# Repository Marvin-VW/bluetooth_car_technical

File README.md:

# 3D-Printed ESP32 RC Car – Complete Project Documentation

## Project Overview
This project consists of a fully 3D-printed RC car based on an ESP32 controller, designed for remote control via a custom-built app.  
All mechanical parts, electronics (PCBs), and software components are fully self-developed or heavily customized.

The vehicle body is based on a DeLorean model (Back to the Future), which has been modified for integration of custom hardware components and a clear interior view.

---

## Features
- **Drive System**:
    - JGB37-520 Motor connected via an axle with ball bearings
    - Front axle controlled by MG90S servo
- **Distance Sensors**:
    - 3x VL53L0X laser distance sensors connected via I2C bus
- **Camera**:
    - ESP32-CAM module for live video streaming over WiFi
- **Lighting**:
    - WS2812C individually addressable LEDs for headlights, taillights, indicators, brake lights, and reverse lights
- **Battery**:
    - 2x Samsung SDI INR18650-35E 3.7V cells (combined to 7.2V system)
- **Charging**:
    - USB-C PD (Power Delivery) charging at 9V/3A via custom charging module
- **Battery Management System (BMS)**:
    - HX-2S-D20 unit for safe charging/discharging

---

## Mechanical Design
- **Chassis**: Modified base from DKS Basics, adjusted for optimized motor mounts, axle supports, battery placement, ESP32 mounting, and PCB integration.
- **Body**: DeLorean STL, modified for wheel clearance, USB-C charging access, and removal of windows for better visibility of internal components.
- **3D Printed Parts**:
    - Chassis components
    - Gear holders and servo brackets
    - Motor mounts
    - Sensor mounts
    - Battery compartments
    - LED lighting holders

---

## Bill of Materials (BOM)

| Component                   | Description                                           |
|------------------------------|-------------------------------------------------------|
| ESP32                        | Main microcontroller                                 |
| JGB37-520 Motor              | Drive motor                                           |
| MG90S Servo                  | Steering servo                                        |
| 3x VL53L0X                   | Distance sensors (I2C bus)                           |
| 2x Samsung INR18650-35E      | Battery cells                                         |
| INA3221                      | Triple current monitor                               |
| HX-2S-D20                    | 2S BMS for battery management                        |
| ESP32-CAM                    | Camera module                                         |
| WS2812C LED Strip            | Addressable LEDs for lighting                        |
| Custom Power PCB             | Power regulation and distribution board             |
| Custom ESP32 PCB             | ESP32 interface board                               |
| Front LED PCBs (x2 variants) | Strip & individual LED board for front lighting      |
| Rear LED PCBs (x2 variants)  | Strip & individual LED board for rear lighting       |
| 3D Printed Parts             | Chassis, body, mounting structures                   |
| USB-C Charging Module        | USB-PD fast charging support                         |
| Bearings, Gears, Shafts      | Mechanical components                               |

---

## Repository Structure

```bash
/3d-printed-esp32-rc-car
│
├── 3d_printed_parts/             # STL files for chassis and case
│
├── pcbs/
│   ├── power_pcb/                # KiCad files and Gerbers for power management board
│   ├── esp32_pcb/                # KiCad files and Gerbers for ESP32 connection board
│   ├── lighting_pcbs/
│   │   ├── front_strip_version/  # PCB for front LED strip mounting
│   │   ├── front_single_led/     # PCB for front individual LEDs
│   │   ├── rear_strip_version/   # PCB for rear LED strip mounting
│   │   └── rear_single_led/      # PCB for rear individual LEDs
│
├── firmware/                     # (External Link: [ESP32 Firmware Repo](https://github.com/Marvin-VW/bluetooth_car_cpp))
│
├── app/                          # (External Link: [Mobile App Repo](https://github.com/Marvin-VW/spring_rest_todo_app))
│
├── images/                       # Photos, renderings, diagrams
│
└── README.md                     # This file
```

---

## Electronic Architecture

### Main Boards:
- **Power PCB**:
    - Battery management (charging/discharging)
    - 5V and 6.6V regulated outputs
    - INA3221 triple current sensor
    - Connectors for servo, distance sensors, motor
- **ESP32 PCB**:
    - Dedicated ESP32 interface
    - Connection to power PCB via a 2x7 (14-pin) connector

### Lighting Boards:
- **Front LED Boards**:
    - *LED Strip Version*: For easier integration of flexible LED strips (WS2812C-compatible)
    - *Individual LED Version*: For precise placement of discrete WS2812C LEDs
- **Rear LED Boards**:
    - *LED Strip Version*
    - *Individual LED Version*

Each lighting board is tailored to fit into designated 3D printed holders.

---

Note: Pins not accurate.

---

## Build and Assembly

1. **3D Print Parts**  
   Print all required STL files using PLA or PETG for maximum durability.

2. **Assemble Electronics**
    - Solder PCBs based on provided KiCad projects.
    - Install the Power PCB, ESP32 PCB, distance sensors, and LEDs.

3. **Mechanical Assembly**
    - Mount motor, servo, and axles with ball bearings.
    - Install batteries, boards, and secure the chassis components.

4. **Install Firmware**
    - Flash the ESP32 using the firmware available in the firmware repository.

5. **App Setup**
    - Install the mobile app to control the car via WiFi.

6. **Testing and Calibration**
    - Test motor, servo, sensors, and LEDs individually before full operation.

---

## License
MIT License

---

## Contributions
Contributions, issues, and feature requests are welcome! Feel free to check the [issues page](#).

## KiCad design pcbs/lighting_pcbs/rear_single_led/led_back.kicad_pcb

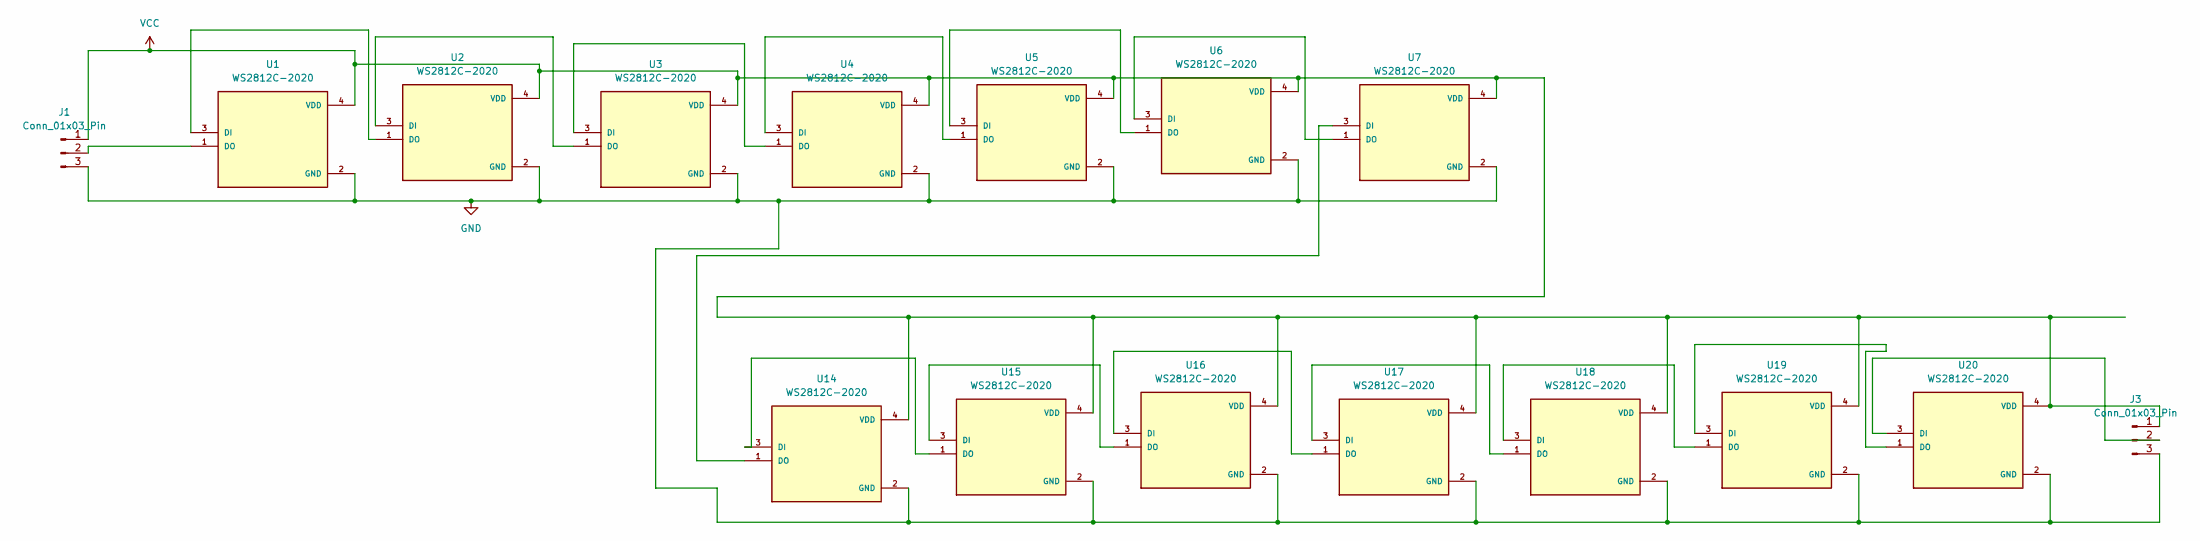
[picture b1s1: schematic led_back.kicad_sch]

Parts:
J1, J3: Conn_01x03_Pin; PinHeader_1x03_P2.54mm_Vertical
U1, U2, U3, U4, U5, U6, U7, U14, U15, U16, U17, U18, U19, U20: WS2812C-2020; LED_WS2812C-2020; PARTREV V1.0

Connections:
GND: J1.3, J3.3, U1.2 (GND), U2.2 (GND), U3.2 (GND), U4.2 (GND), U5.2 (GND), U6.2 (GND), U7.2 (GND), U14.2 (GND), U15.2 (GND), U16.2 (GND), U17.2 (GND), U18.2 (GND), U19.2 (GND), U20.2 (GND)
unnamed: J1.2, U1.1 (DO)
unnamed: J3.2, U20.3 (DI)
unnamed: U1.3 (DI), U2.1 (DO)
unnamed: U2.3 (DI), U3.1 (DO)
unnamed: U3.3 (DI), U4.1 (DO)
unnamed: U4.3 (DI), U5.1 (DO)
unnamed: U5.3 (DI), U6.1 (DO)
unnamed: U6.3 (DI), U7.1 (DO)
unnamed: U14.3 (DI), U15.1 (DO)
unnamed: U7.3 (DI), U14.1 (DO)
unnamed: U15.3 (DI), U16.1 (DO)
unnamed: U16.3 (DI), U17.1 (DO)
unnamed: U17.3 (DI), U18.1 (DO)
unnamed: U18.3 (DI), U19.1 (DO)
unnamed: U19.3 (DI), U20.1 (DO)
VCC: J1.1, J3.1, U1.4 (VDD), U2.4 (VDD), U3.4 (VDD), U4.4 (VDD), U5.4 (VDD), U6.4 (VDD), U7.4 (VDD), U14.4 (VDD), U15.4 (VDD), U16.4 (VDD), U17.4 (VDD), U18.4 (VDD), U19.4 (VDD), U20.4 (VDD)

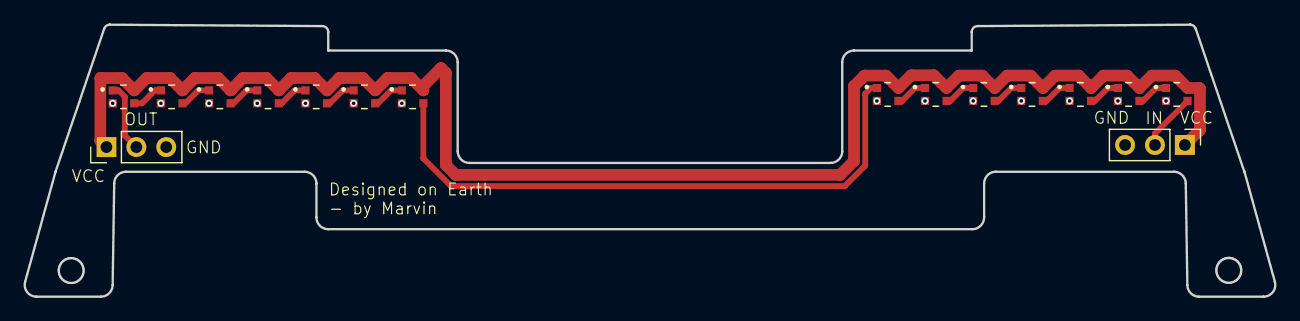
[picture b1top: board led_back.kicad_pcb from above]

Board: 2 copper layers, 106.2 x 23.1 mm, 16 parts (0 on the bottom side), 17 nets.

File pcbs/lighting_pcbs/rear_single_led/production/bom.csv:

Designator,Footprint,Quantity,Value,LCSC Part #
"_2, ",,2,,
"J1, J3",PinHeader_1x03_P2.54mm_Vertical,2,Conn_01x03_Pin,
"U1, U14, U15, U16, U17, U18, U19, U2, U20, U3, U4, U5, U6, U7",LED_WS2812C-2020,14,WS2812C-2020,

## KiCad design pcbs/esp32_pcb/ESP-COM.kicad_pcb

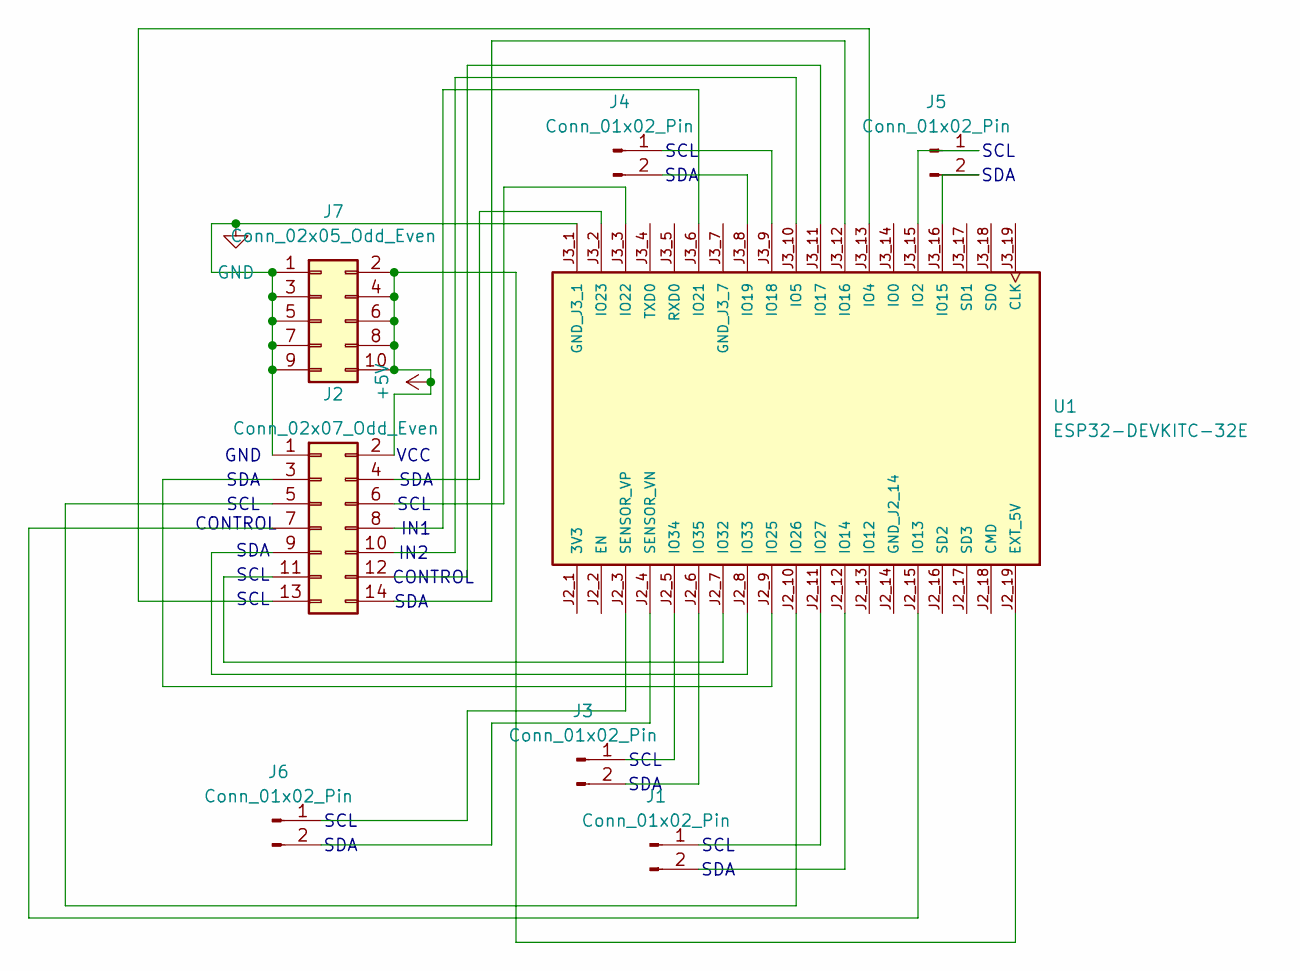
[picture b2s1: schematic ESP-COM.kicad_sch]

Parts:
J1, J3, J4, J5, J6: Conn_01x02_Pin; PinHeader_1x02_P2.54mm_Vertical
J2: Conn_02x07_Odd_Even; PinHeader_2x07_P2.54mm_Vertical
J7: Conn_02x05_Odd_Even; PinHeader_2x05_P2.54mm_Vertical
U1: ESP32-DEVKITC-32E; MODULE_ESP32-DEVKITC-32E; PARTREV 1.4

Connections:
+5V: J2.2, J7.2, J7.4, J7.6, J7.8, J7.10, U1.J2_19 (EXT_5V)
GND: J2.1, J7.1, J7.3, J7.5, J7.7, J7.9, U1.J3_1 (GND_J3_1)
unnamed: J1.1, U1.J2_11 (IO27)
unnamed: J1.2, U1.J2_12 (IO14)
unnamed: J2.3, U1.J2_9 (IO25)
unnamed: J2.4, U1.J3_2 (IO23)
unnamed: J2.5, U1.J2_10 (IO26)
unnamed: J2.6, U1.J3_3 (IO22)
unnamed: J2.7, U1.J2_15 (IO13)
unnamed: J2.8, U1.J3_6 (IO21)
unnamed: J2.9, U1.J2_8 (IO33)
unnamed: J2.10, U1.J3_10 (IO5)
unnamed: J2.11, U1.J2_7 (IO32)
unnamed: J2.12, U1.J3_11 (IO17)
unnamed: J2.13, U1.J3_13 (IO4)
unnamed: J2.14, U1.J3_12 (IO16)
unnamed: J3.1, U1.J2_5 (IO34)
unnamed: J3.2, U1.J2_6 (IO35)
unnamed: J4.1, U1.J3_9 (IO18)
unnamed: J4.2, U1.J3_8 (IO19)
unnamed: J5.1, U1.J3_15 (IO2)
unnamed: J5.2, U1.J3_16 (IO15)
unnamed: J6.1, U1.J2_3 (SENSOR_VP)
unnamed: J6.2, U1.J2_4 (SENSOR_VN)

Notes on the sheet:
SDA
SCL
IN1
CONTROL
GND
VCC
IN2

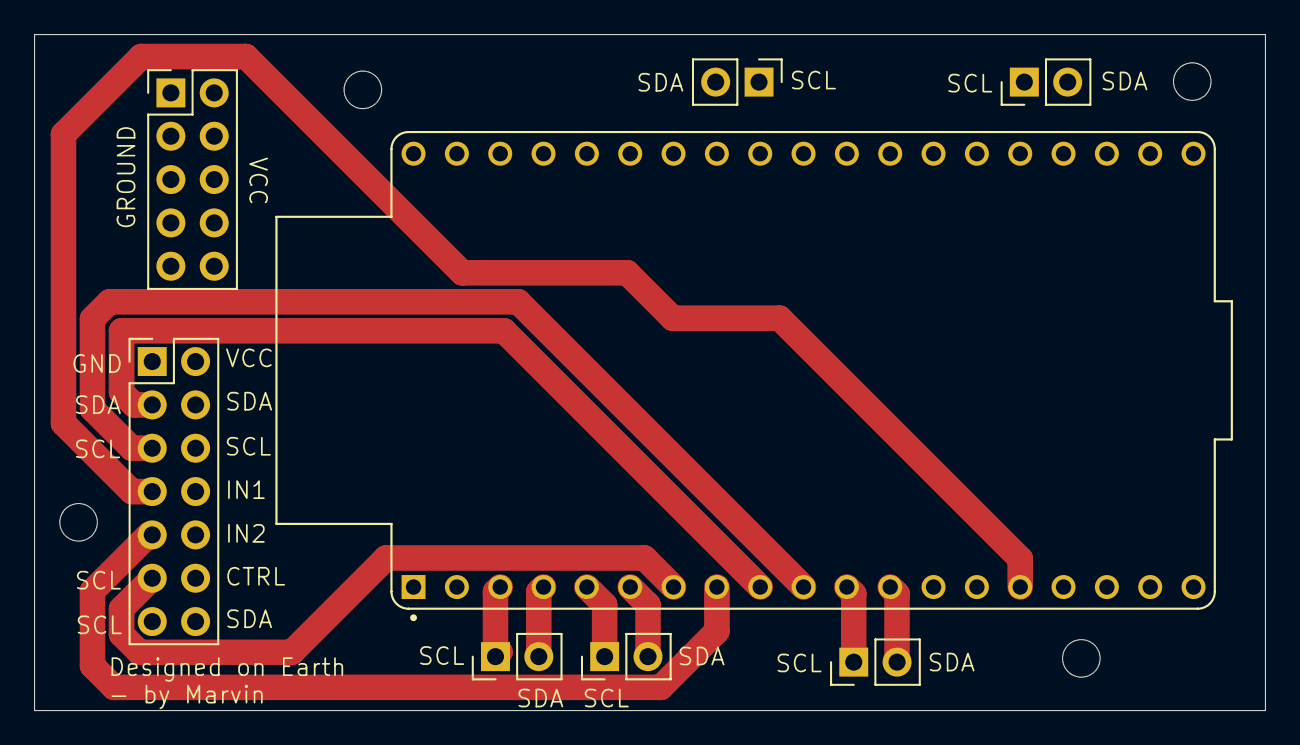
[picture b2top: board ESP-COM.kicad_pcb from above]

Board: 4 copper layers, 72.1 x 39.6 mm, 8 parts (0 on the bottom side), 24 nets.

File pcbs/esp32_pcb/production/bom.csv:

Designator,Footprint,Quantity,Value,LCSC Part #
"J1, J3, J4, J5, J6",PinHeader_1x02_P2.54mm_Vertical,5,Conn_01x02_Pin,
J2,PinHeader_2x07_P2.54mm_Vertical,1,Conn_02x07_Odd_Even,
J7,PinHeader_2x05_P2.54mm_Vertical,1,Conn_02x05_Odd_Even,
U1,MODULE_ESP32-DEVKITC-32E,1,ESP32-DEVKITC-32E,

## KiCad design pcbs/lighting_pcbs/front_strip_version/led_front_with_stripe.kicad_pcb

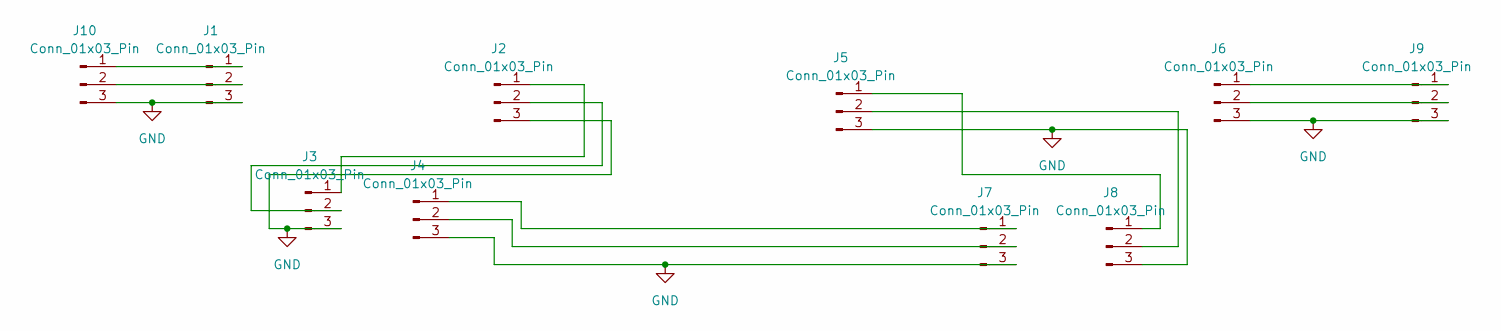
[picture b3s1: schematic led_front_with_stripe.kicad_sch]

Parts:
J1, J2, J3, J4, J5, J6, J7, J8: Conn_01x03_Pin; led_pads
J9, J10: Conn_01x03_Pin; PinHeader_1x03_P2.54mm_Vertical

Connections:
GND: J1.3, J2.3, J3.3, J4.3, J5.3, J6.3, J7.3, J8.3, J9.3, J10.3
unnamed: J1.1, J10.1
unnamed: J1.2, J10.2
unnamed: J2.1, J3.1
unnamed: J2.2, J3.2
unnamed: J4.1, J7.1
unnamed: J4.2, J7.2
unnamed: J5.1, J8.1
unnamed: J5.2, J8.2
unnamed: J6.1, J9.1
unnamed: J6.2, J9.2

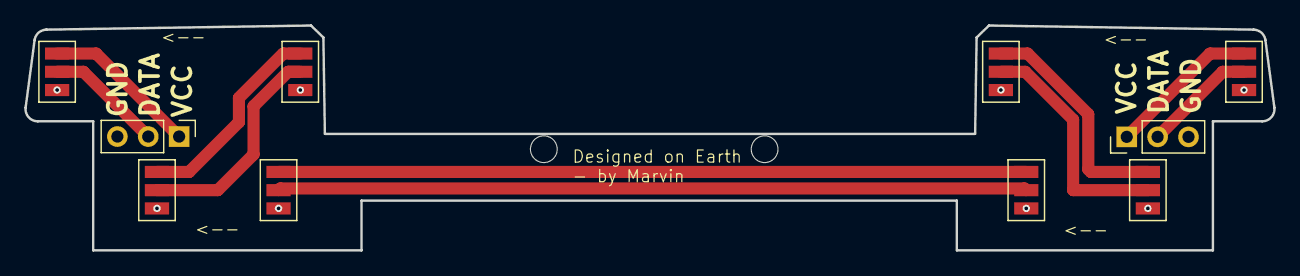
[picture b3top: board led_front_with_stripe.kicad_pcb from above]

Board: 2 copper layers, 102.7 x 18.5 mm, 10 parts (0 on the bottom side), 11 nets.

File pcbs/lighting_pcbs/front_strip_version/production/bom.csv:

Designator,Footprint,Quantity,Value,LCSC Part #
"_2, ",,2,,
"J1, J2, J3, J4, J5, J6, J7, J8",led_pads,8,Conn_01x03_Pin,
"J10, J9",PinHeader_1x03_P2.54mm_Vertical,2,Conn_01x03_Pin,

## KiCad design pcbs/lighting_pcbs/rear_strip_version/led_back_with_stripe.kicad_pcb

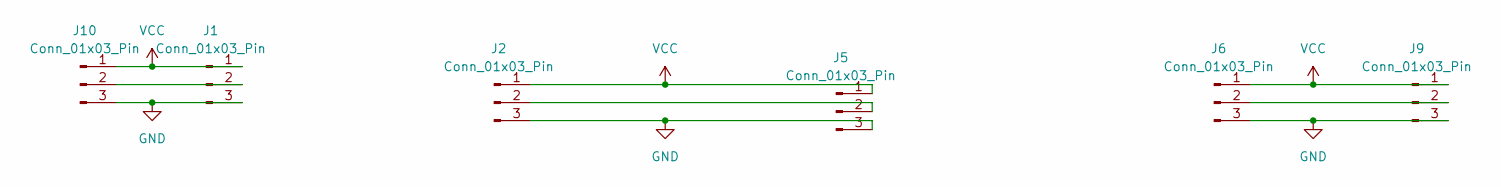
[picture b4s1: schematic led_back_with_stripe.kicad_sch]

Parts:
J1, J2, J5, J6: Conn_01x03_Pin; led_pads
J9, J10: Conn_01x03_Pin; PinHeader_1x03_P2.54mm_Vertical

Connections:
GND: J1.3, J2.3, J5.3, J6.3, J9.3, J10.3
unnamed: J1.2, J10.2
unnamed: J2.2, J5.2
unnamed: J6.2, J9.2
VCC: J1.1, J2.1, J5.1, J6.1, J9.1, J10.1

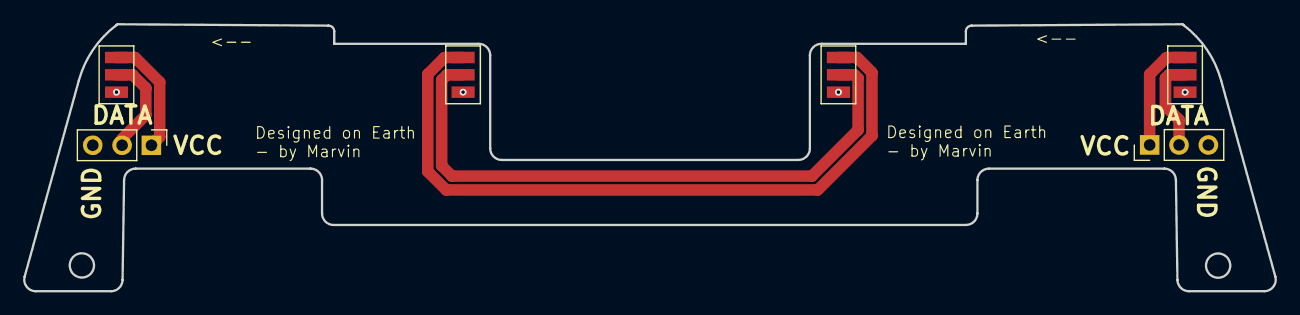
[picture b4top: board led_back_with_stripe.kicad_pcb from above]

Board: 2 copper layers, 108.3 x 23.1 mm, 6 parts (0 on the bottom side), 5 nets.

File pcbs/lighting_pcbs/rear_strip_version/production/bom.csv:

Designator,Footprint,Quantity,Value,LCSC Part #
"J1, J2, J5, J6",led_pads,4,Conn_01x03_Pin,
"J10, J9",PinHeader_1x03_P2.54mm_Vertical,2,Conn_01x03_Pin,

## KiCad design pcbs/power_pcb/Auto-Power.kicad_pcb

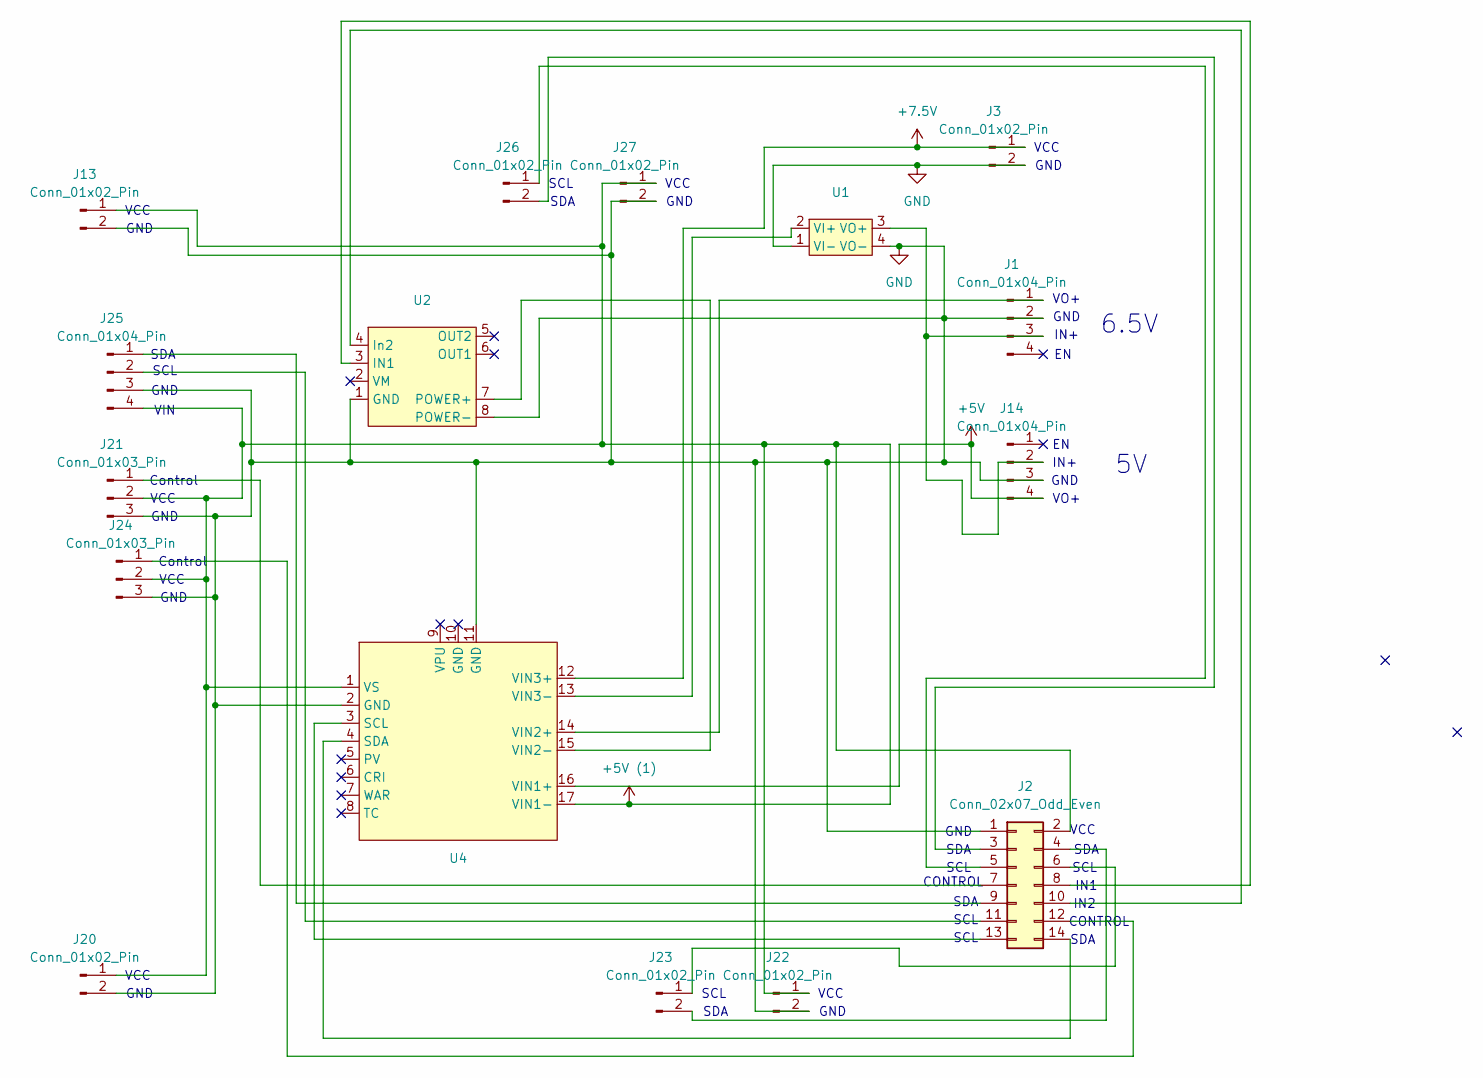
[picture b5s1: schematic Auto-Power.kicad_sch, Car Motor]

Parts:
J1, J14, J25: Conn_01x04_Pin; PinHeader_1x04_P2.54mm_Vertical
J2: Conn_02x07_Odd_Even; PinHeader_2x07_P2.54mm_Vertical
J3, J13, J20, J22, J23, J26, J27: Conn_01x02_Pin; PinHeader_1x02_P2.54mm_Vertical
J21, J24: Conn_01x03_Pin; PinHeader_1x03_P2.54mm_Vertical
U1: anti_reverse
U2: DRV8871
U4: INA3221_Module

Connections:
+5V: J14.4, U4.16 (VIN1+)
+5V (1): J2.2, J13.1, J20.1, J21.2, J22.1, J24.2, J25.4, J27.1, U4.1 (VS), U4.17 (VIN1-)
+7.5V: J3.1, U4.12 (VIN3+)
GND: J1.2, J2.1, J3.2, J13.2, J14.3, J20.2, J21.3, J22.2, J24.3, J25.3, J27.2, U1.1 (VI-), U1.4 (VO-), U2.1 (GND), U2.8 (POWER-), U4.2 (GND), U4.11 (GND)
unnamed: J1.1, U4.14 (VIN2+)
unnamed: J1.3, J14.2, U1.3 (VO+)
unnamed: J2.3, J26.2
unnamed: J2.4, J23.2
unnamed: J2.5, J26.1
unnamed: J2.6, J23.1
unnamed: J2.7, J21.1
unnamed: J2.8, U2.3 (IN1)
unnamed: J2.9, J25.1
unnamed: J2.10, U2.4 (In2)
unnamed: J2.11, J25.2
unnamed: J2.12, J24.1
unnamed: J2.13, U4.3 (SCL)
unnamed: J2.14, U4.4 (SDA)
unnamed: U1.2 (VI+), U4.13 (VIN3-)
unnamed: U2.7 (POWER+), U4.15 (VIN2-)

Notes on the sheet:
IN2
VCC
SDA
SCL
VIN
VO+
GND
CONTROL
IN+
Control
SCL
6.5V
IN1

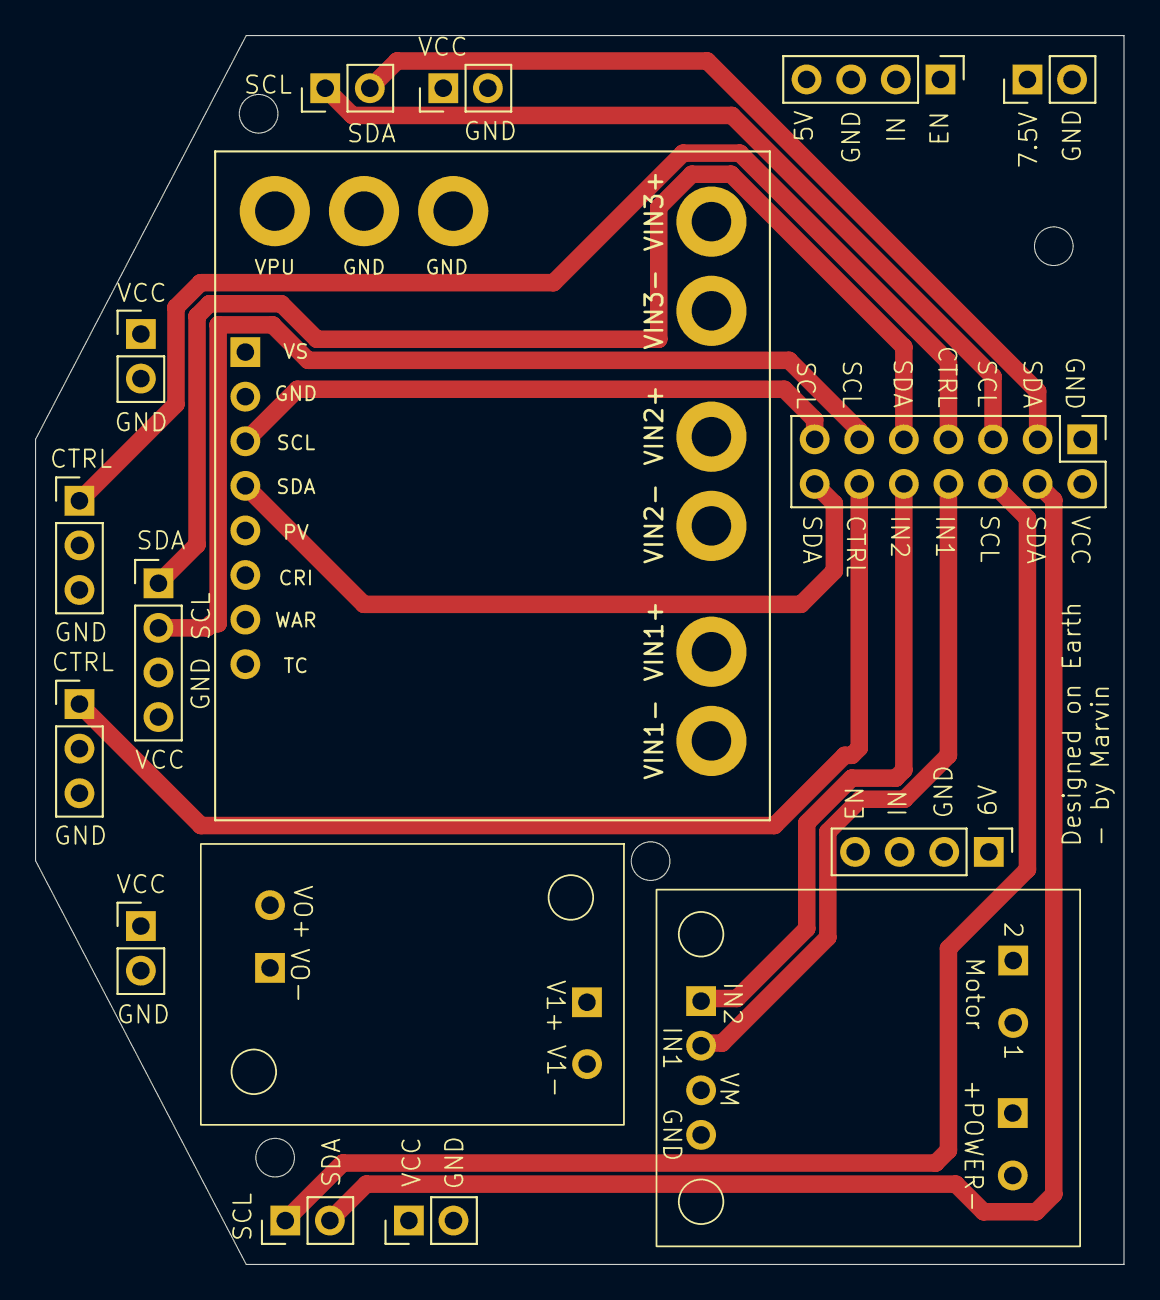
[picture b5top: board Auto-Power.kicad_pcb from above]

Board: 4 copper layers, 62.0 x 70.0 mm, 16 parts (0 on the bottom side), 20 nets.

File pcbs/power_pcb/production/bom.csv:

Designator,Footprint,Quantity,Value,LCSC Part #
"_3, _2, ",,3,,
"J1, J14, J25",PinHeader_1x04_P2.54mm_Vertical,3,Conn_01x04_Pin,
"J13, J20, J22, J23, J26, J27, J3",PinHeader_1x02_P2.54mm_Vertical,7,Conn_01x02_Pin,
J2,PinHeader_2x07_P2.54mm_Vertical,1,Conn_02x07_Odd_Even,
"J21, J24",PinHeader_1x03_P2.54mm_Vertical,2,Conn_01x03_Pin,
U1,anti_reverse,1,~,
U2,DRV8871,1,~,
U4,INA3221_Module,1,~,

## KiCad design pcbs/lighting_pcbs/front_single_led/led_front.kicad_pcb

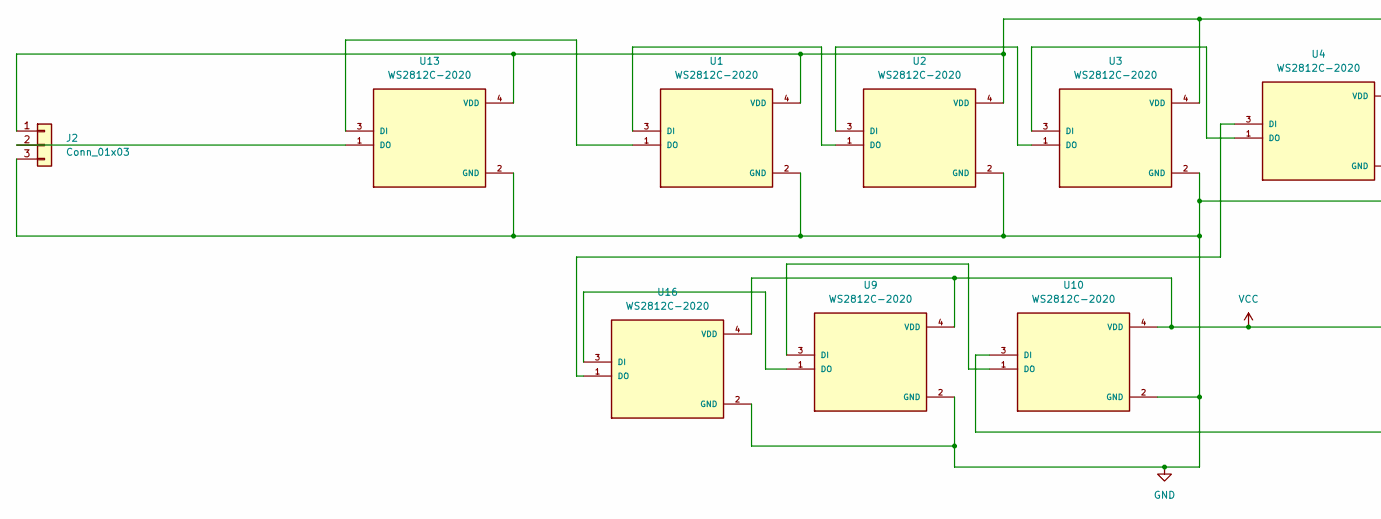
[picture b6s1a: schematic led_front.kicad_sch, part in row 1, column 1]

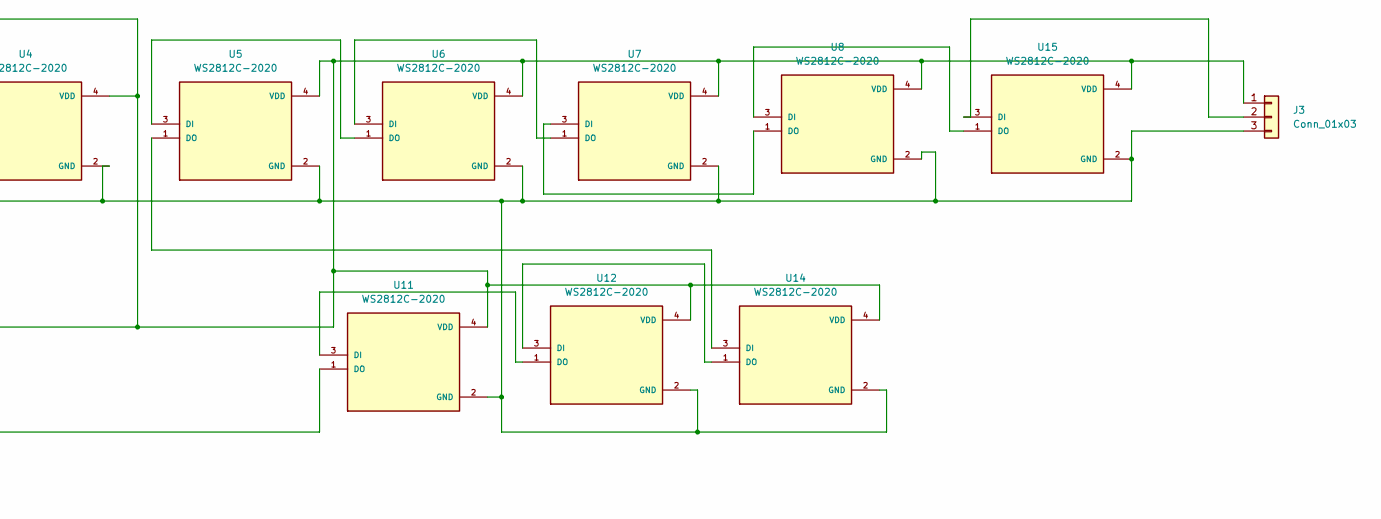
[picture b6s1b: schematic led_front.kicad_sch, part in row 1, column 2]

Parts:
J2, J3: Conn_01x03; PinHeader_1x03_P2.54mm_Vertical
U1, U2, U3, U4, U5, U6, U7, U8, U9, U10, U11, U12, U13, U14, U15, U16: WS2812C-2020; LED_WS2812C-2020; PARTREV V1.0

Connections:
GND: J2.3, J3.3, U1.2 (GND), U2.2 (GND), U3.2 (GND), U4.2 (GND), U5.2 (GND), U6.2 (GND), U7.2 (GND), U8.2 (GND), U9.2 (GND), U10.2 (GND), U11.2 (GND), U12.2 (GND), U13.2 (GND), U14.2 (GND), U15.2 (GND), U16.2 (GND)
unnamed: J2.2, U13.1 (DO)
unnamed: J3.2, U15.3 (DI)
unnamed: U1.3 (DI), U2.1 (DO)
unnamed: U1.1 (DO), U13.3 (DI)
unnamed: U2.3 (DI), U3.1 (DO)
unnamed: U3.3 (DI), U4.1 (DO)
unnamed: U5.3 (DI), U6.1 (DO)
unnamed: U6.3 (DI), U7.1 (DO)
unnamed: U7.3 (DI), U8.1 (DO)
unnamed: U10.3 (DI), U11.1 (DO)
unnamed: U9.3 (DI), U10.1 (DO)
unnamed: U11.3 (DI), U12.1 (DO)
unnamed: U12.3 (DI), U14.1 (DO)
unnamed: U5.1 (DO), U14.3 (DI)
unnamed: U8.3 (DI), U15.1 (DO)
unnamed: U9.1 (DO), U16.3 (DI)
unnamed: U4.3 (DI), U16.1 (DO)
VCC: J2.1, J3.1, U1.4 (VDD), U2.4 (VDD), U3.4 (VDD), U4.4 (VDD), U5.4 (VDD), U6.4 (VDD), U7.4 (VDD), U8.4 (VDD), U9.4 (VDD), U10.4 (VDD), U11.4 (VDD), U12.4 (VDD), U13.4 (VDD), U14.4 (VDD), U15.4 (VDD), U16.4 (VDD)

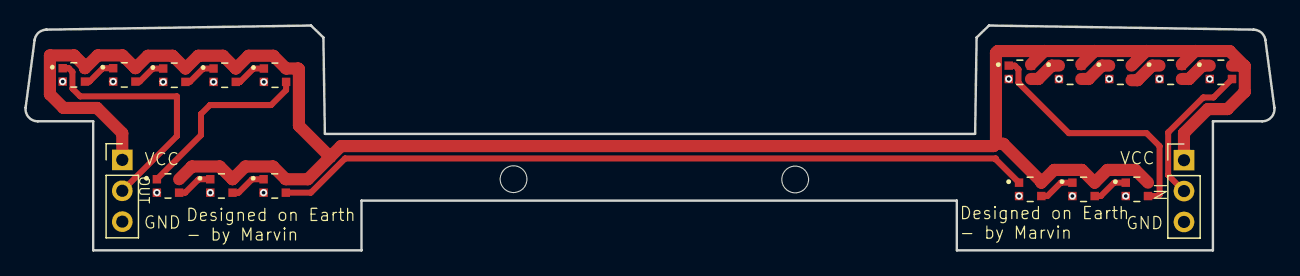
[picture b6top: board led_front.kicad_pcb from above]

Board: 2 copper layers, 102.7 x 18.5 mm, 18 parts (0 on the bottom side), 19 nets.

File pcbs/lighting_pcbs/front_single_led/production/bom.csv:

Designator,Footprint,Quantity,Value,LCSC Part #
"_2, ",,2,,
"J2, J3",PinHeader_1x03_P2.54mm_Vertical,2,Conn_01x03,
"U1, U10, U11, U12, U13, U14, U15, U16, U2, U3, U4, U5, U6, U7, U8, U9",LED_WS2812C-2020,16,WS2812C-2020,

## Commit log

2025-04-28 init
2025-05-25 Create LICENSE
